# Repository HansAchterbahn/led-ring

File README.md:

# LED Ring

A simple LED ring with twelve 3 mm LEDs and i2c interface. Created to use with a [CIRQUE TM035035 touch pad](https://www.cirque.com/glidepoint-circle-trackpads). Its 12 positions makes it suitable for clock applications.

I use this PCB in my [bottle-light](https://github.com/HansAchterbahn/bottle-light) project.

*Fork me and have fun!*

## Schematic

## Board

## 3D View (Fusion360)

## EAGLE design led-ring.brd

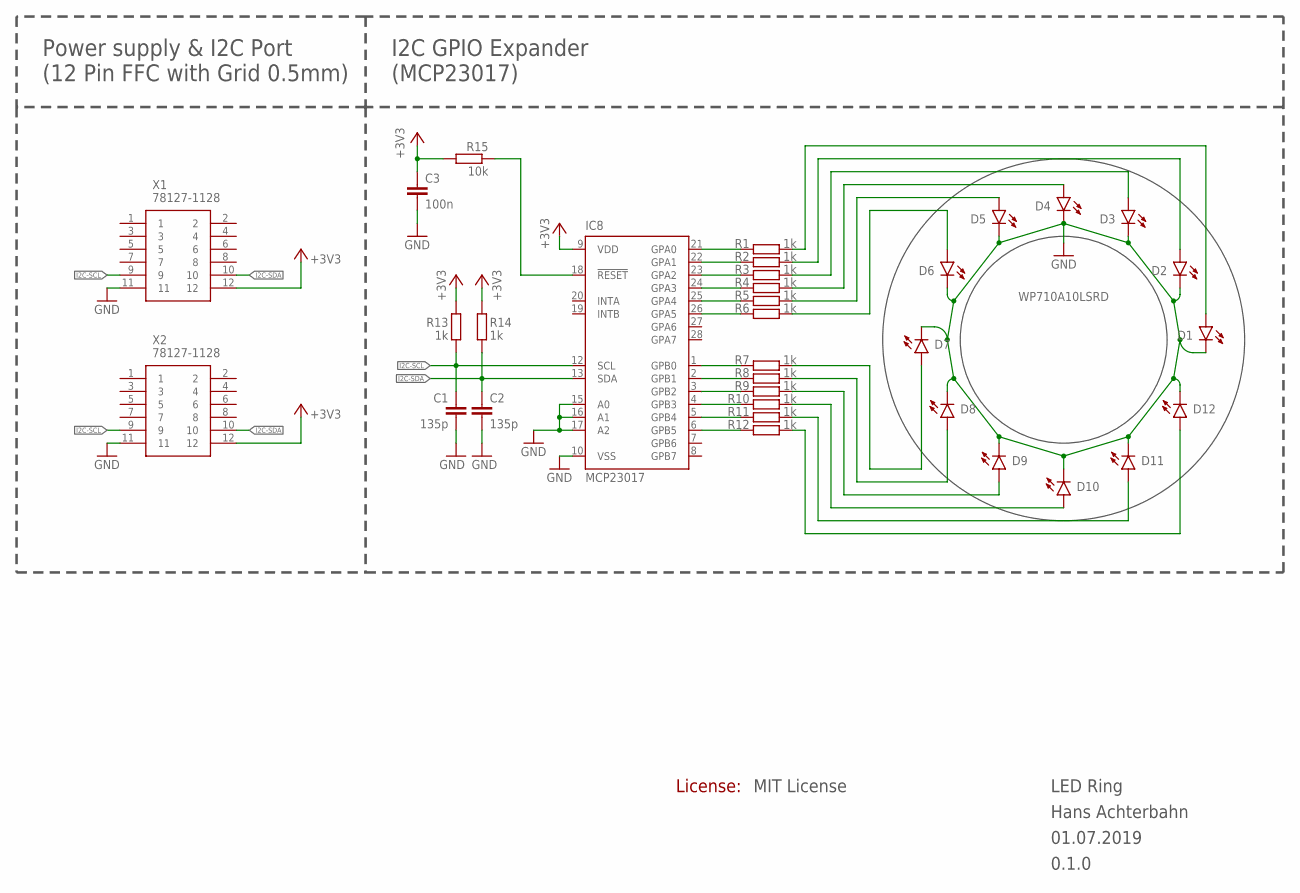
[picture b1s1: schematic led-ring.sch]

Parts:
C1, C2: 135p; C0603
C3: 100n; C0603; MOUSER 581-0603YC104J
D1, D2, D3, D4, D5, D6, D7, D8, D9, D10, D11, D12: WP710A10LSRD; RADIAL_3MM
IC8: MCP23017; SOP65P780X200-28; MOUSER 579-MCP23017-E/SS
R1, R2, R3, R4, R5, R6, R7, R8, R9, R10, R11, R12, R13, R14: 1k; R0603
R15: 10k; R0603; MOUSER 71-CRCW0603-10K-E3
X1, X2: 78127-1128; 781271128

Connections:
+3V3: C3.1, IC8.9 (VDD), R13.1, R14.1, R15.2, X1.12, X2.12
GND: C1.2, C2.2, C3.2, D1.C, D2.C, D3.C, D4.C, D5.C, D6.C, D7.C, D8.C, D9.C, D10.C, D11.C, D12.C, IC8.10 (VSS), IC8.15 (A0), IC8.16 (A1), IC8.17 (A2), X1.11, X2.11
I2C-SCL: C1.1, IC8.12 (SCL), R13.2, X1.9, X2.9
I2C-SDA: C2.1, IC8.13 (SDA), R14.2, X1.10, X2.10
LED-01: D1.A, R1.1
LED-02: D2.A, R2.1
LED-03: D3.A, R3.1
LED-04: D4.A, R4.1
LED-05: D5.A, R5.1
LED-06: D6.A, R6.1
LED-07: D7.A, R7.1
LED-08: D8.A, R8.1
LED-09: D9.A, R9.1
LED-10: D10.A, R10.1
LED-11: D11.A, R11.1
LED-12: D12.A, R12.1
unnamed: IC8.26 (GPA5), R6.2
unnamed: IC8.21 (GPA0), R1.2
unnamed: IC8.22 (GPA1), R2.2
unnamed: IC8.23 (GPA2), R3.2
unnamed: IC8.24 (GPA3), R4.2
unnamed: IC8.25 (GPA4), R5.2
unnamed: IC8.1 (GPB0), R7.2
unnamed: IC8.2 (GPB1), R8.2
unnamed: IC8.3 (GPB2), R9.2
unnamed: IC8.4 (GPB3), R10.2
unnamed: IC8.5 (GPB4), R11.2
unnamed: IC8.6 (GPB5), R12.2
unnamed: IC8.18 (!RESET), R15.1

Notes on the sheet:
License:
I2C GPIO Expander (MCP23017)
Power supply & I2C Port (12 Pin FFC with Grid 0.5mm)

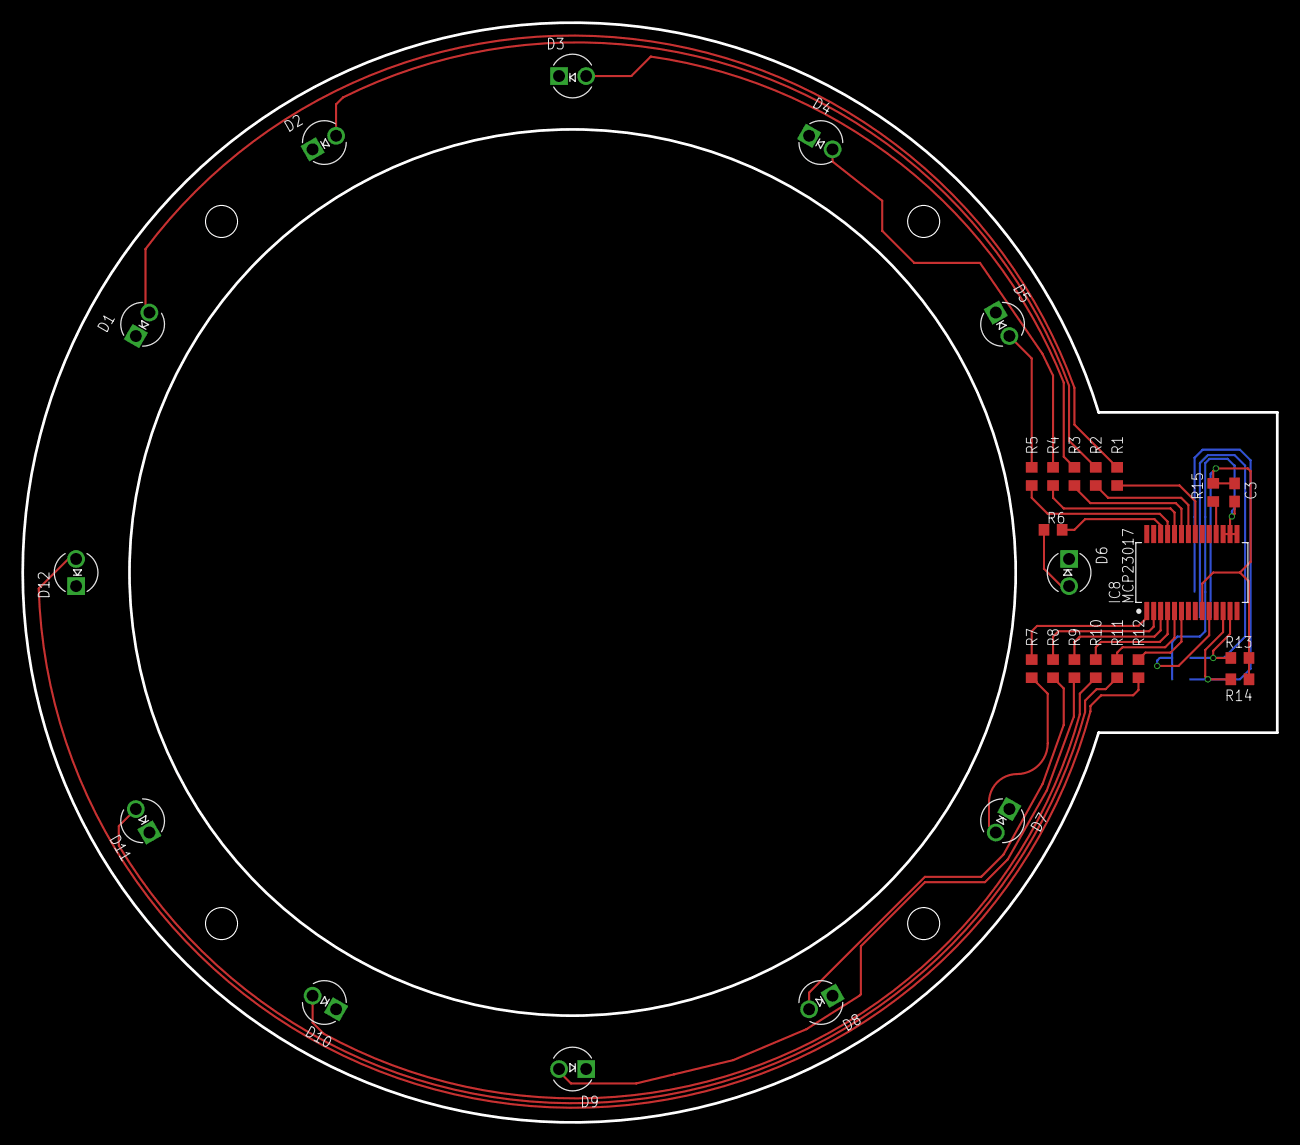
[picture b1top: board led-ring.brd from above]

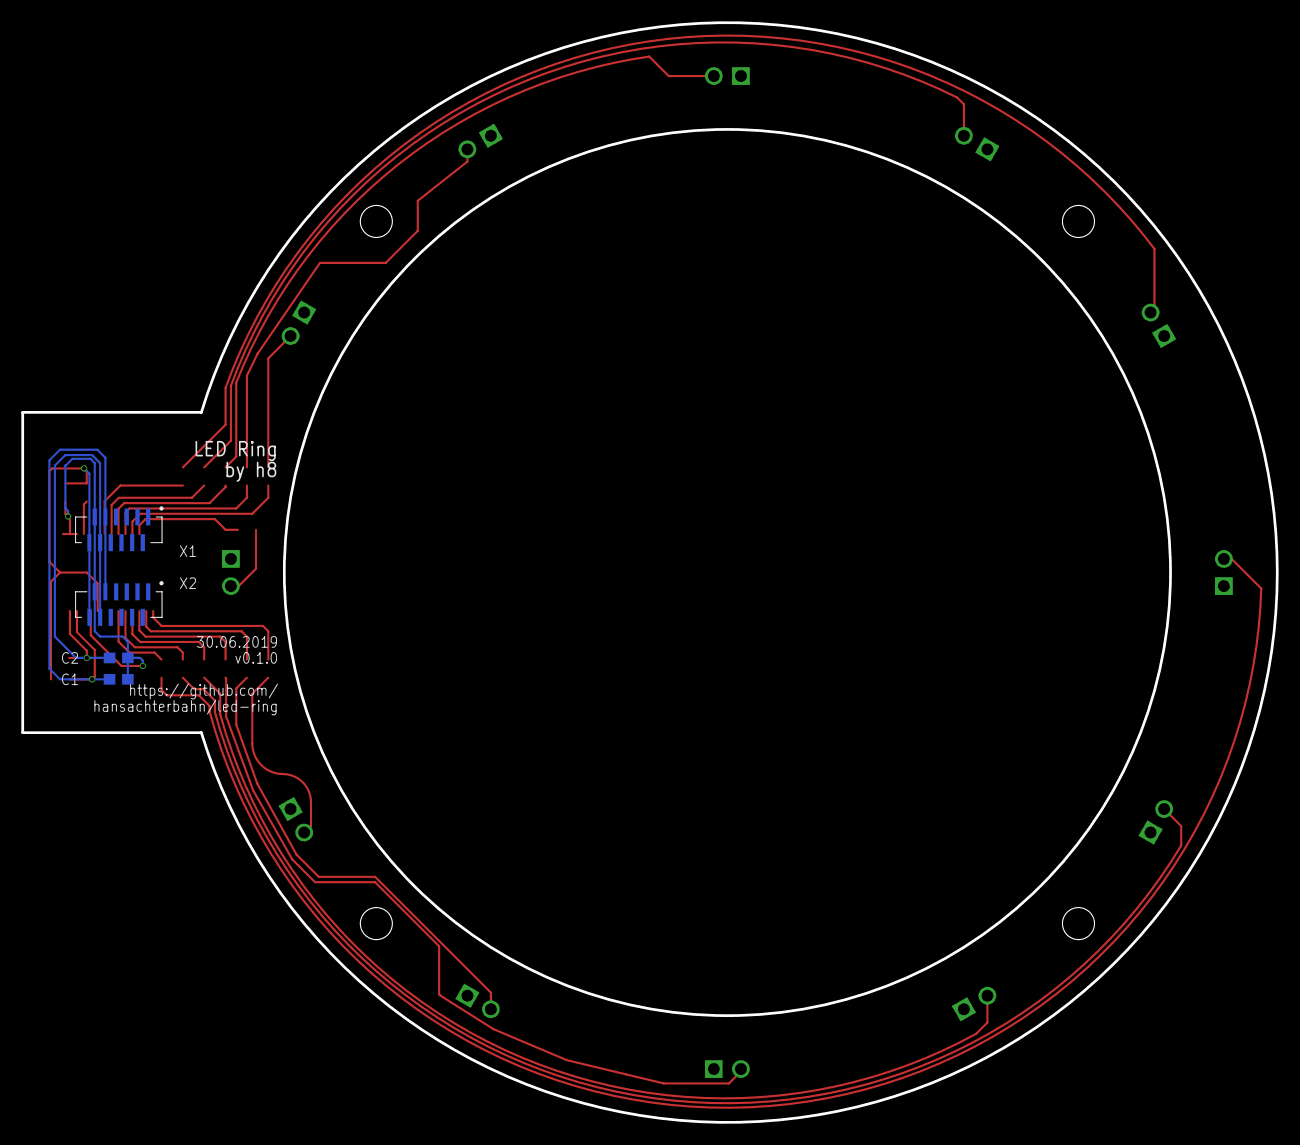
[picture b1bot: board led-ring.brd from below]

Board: 2 copper layers, 117.5 x 103.0 mm, 34 parts (4 on the bottom side), 29 nets.

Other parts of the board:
U$1: A4L-LOC

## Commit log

2019-06-30 developed a simple LED ring with i2c interface
2019-06-30 Doku pictures and update README
2019-07-01 beautified schematic | added i2c pull up resistors | beauty corrections on the board
2019-07-01 Update README | added pictures of schematic and board
2019-07-04 changed some footprint drawings

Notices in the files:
led-ring.sch:
LICENSE: MIT License
